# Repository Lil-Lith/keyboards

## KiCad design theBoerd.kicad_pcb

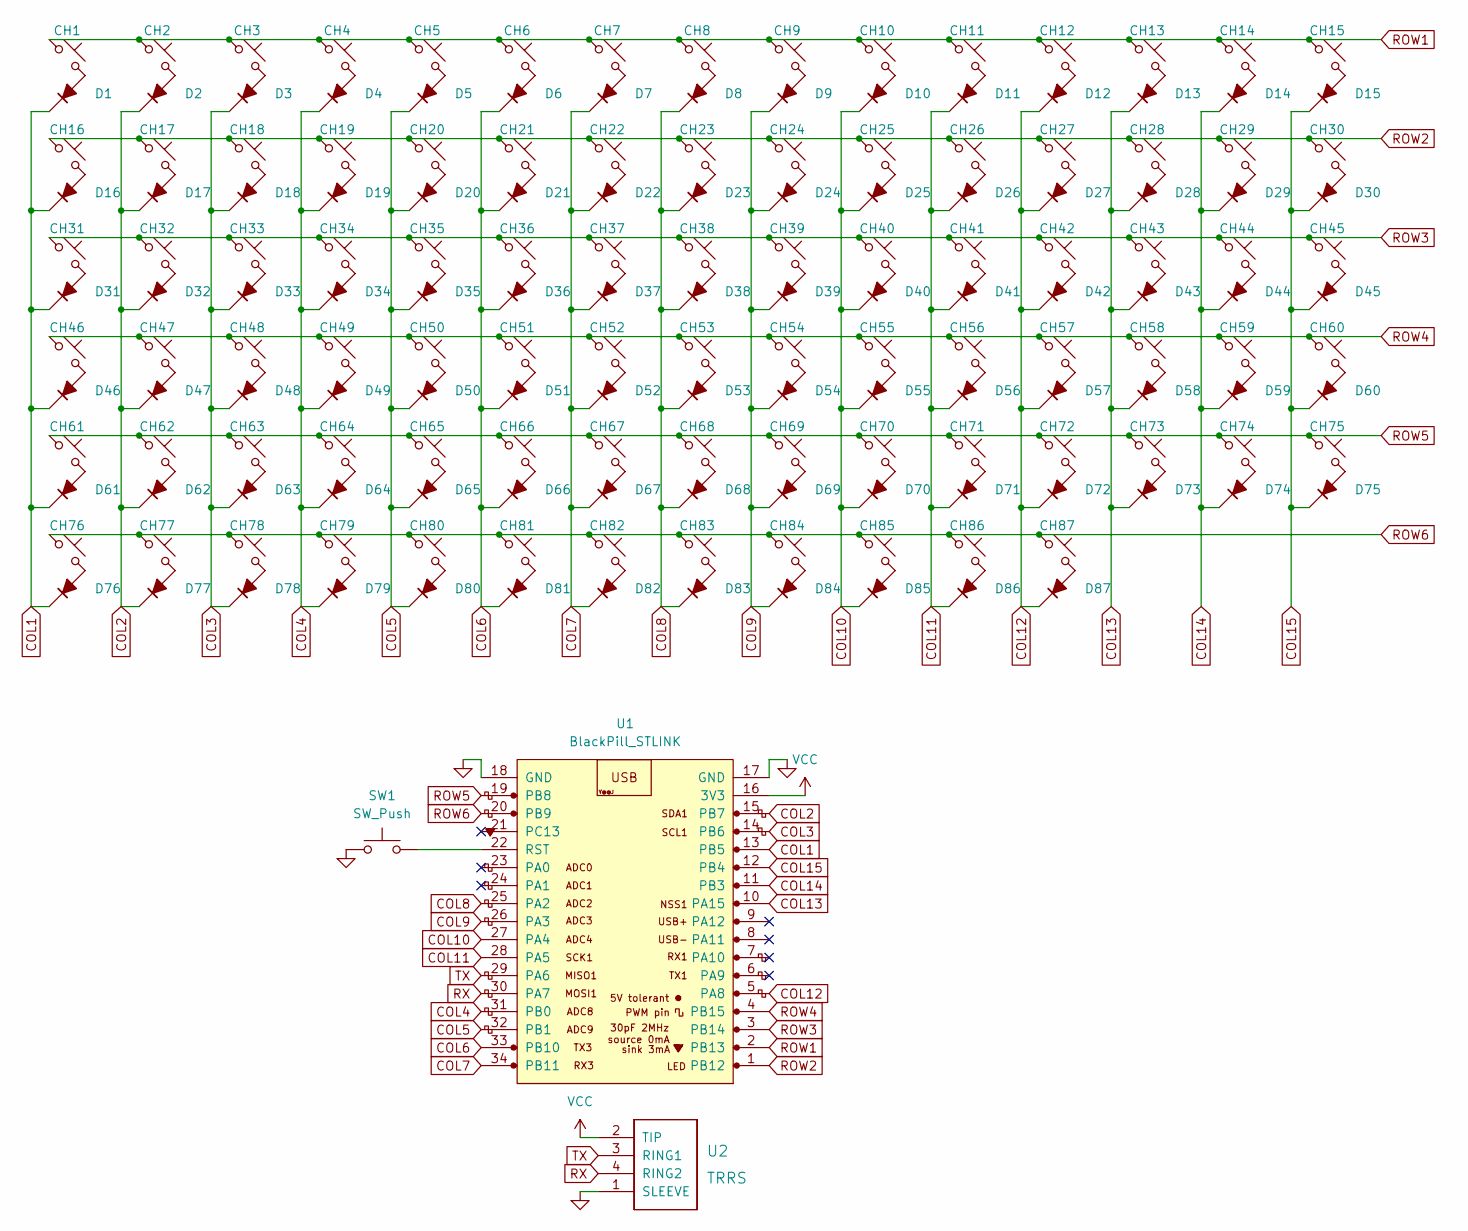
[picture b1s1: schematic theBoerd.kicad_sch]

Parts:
CH1, CH2, CH3, CH4, CH5, CH6, CH7, CH8, CH9, CH10, CH11, CH12, CH13, CH14, CH15, CH16, CH17, CH18, CH19, CH20, CH21, CH22, CH23, CH24, CH25, CH26, CH27, CH28, CH29, CH32, CH33, CH34, CH35, CH36, CH37, CH38, CH39, CH40, CH41, CH42, CH43, CH45, CH46, CH47, CH49, CH50, CH51, CH52, CH53, CH54, CH55, CH56, CH57, CH58, CH59, CH61, CH62, CH63, CH65, CH66, CH67, CH68, CH69, CH70, CH71, CH72, CH73, CH74, CH76, CH77, CH86, CH87: KS33_SW_HS; Gateron-KS33-Hotswap-1U
CH30: KS33_SW_HS; Gateron-KS33-Hotswap-2U
CH31, CH44: KS33_SW_HS; Gateron-KS33-Hotswap-1.5U
CH48: KS33_SW_HS; Gateron-KS33-Hotswap-1.75U
CH60, CH64: KS33_SW_HS; Gateron-KS33-Hotswap-2.25U
CH75: KS33_SW_HS; Gateron-KS33-Hotswap-2.75U
CH78, CH79, CH80, CH82, CH83, CH84, CH85: KS33_SW_HS; Gateron-KS33-Hotswap-1.25U
CH81: KS33_SW_HS; Gateron-KS33-Hotswap-6.25U
D1, D2, D3, D4, D5, D6, D7, D8, D9, D10, D11, D12, D13, D14, D15, D16, D17, D18, D19, D20, D21, D22, D23, D24, D25, D26, D27, D28, D29, D30, D31, D32, D33, D34, D35, D36, D37, D38, D39, D40, D41, D42, D43, D44, D45, D46, D47, D48, D49, D50, D51, D52, D53, D54, D55, D56, D57, D58, D59, D60, D61, D62, D63, D64, D65, D66, D67, D68, D69, D70, D71, D72, D73, D74, D75, D76, D77, D78, D79, D80, D81, D82, D83, D84, D85, D86, D87: D_45deg_Filled; D_1210_3225Metric
SW1: SW_Push; SW_SPDT_REED_MSDM-DT
U1: BlackPill_STLINK
U2: TRRS; TRRS-PJ-320A

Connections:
COL1: D1.1 (K), D16.1 (K), D31.1 (K), D46.1 (K), D61.1 (K), D76.1 (K), U1.13 (PB5)
COL2: D2.1 (K), D17.1 (K), D32.1 (K), D47.1 (K), D62.1 (K), D77.1 (K), U1.15 (PB7)
COL3: D3.1 (K), D18.1 (K), D33.1 (K), D48.1 (K), D63.1 (K), D78.1 (K), U1.14 (PB6)
COL4: D4.1 (K), D19.1 (K), D34.1 (K), D49.1 (K), D64.1 (K), D79.1 (K), U1.31 (PB0)
COL5: D5.1 (K), D20.1 (K), D35.1 (K), D50.1 (K), D65.1 (K), D80.1 (K), U1.32 (PB1)
COL6: D6.1 (K), D21.1 (K), D36.1 (K), D51.1 (K), D66.1 (K), D81.1 (K), U1.33 (PB10)
COL7: D7.1 (K), D22.1 (K), D37.1 (K), D52.1 (K), D67.1 (K), D82.1 (K), U1.34 (PB11)
COL8: D8.1 (K), D23.1 (K), D38.1 (K), D53.1 (K), D68.1 (K), D83.1 (K), U1.25 (PA2)
COL9: D9.1 (K), D24.1 (K), D39.1 (K), D54.1 (K), D69.1 (K), D84.1 (K), U1.26 (PA3)
COL10: D10.1 (K), D25.1 (K), D40.1 (K), D55.1 (K), D70.1 (K), D85.1 (K), U1.27 (PA4)
COL11: D11.1 (K), D26.1 (K), D41.1 (K), D56.1 (K), D71.1 (K), D86.1 (K), U1.28 (PA5)
COL12: D12.1 (K), D27.1 (K), D42.1 (K), D57.1 (K), D72.1 (K), D87.1 (K), U1.5 (PA8)
COL13: D13.1 (K), D28.1 (K), D43.1 (K), D58.1 (K), D73.1 (K), U1.10 (PA15)
COL14: D14.1 (K), D29.1 (K), D44.1 (K), D59.1 (K), D74.1 (K), U1.11 (PB3)
COL15: D15.1 (K), D30.1 (K), D45.1 (K), D60.1 (K), D75.1 (K), U1.12 (PB4)
GND: SW1.1, U1.17 (GND), U1.18 (GND), U2.1 (SLEEVE)
unnamed: CH1.2, D1.2 (A)
unnamed: CH2.2, D2.2 (A)
unnamed: CH3.2, D3.2 (A)
unnamed: CH4.2, D4.2 (A)
unnamed: CH5.2, D5.2 (A)
unnamed: CH6.2, D6.2 (A)
unnamed: CH7.2, D7.2 (A)
unnamed: CH8.2, D8.2 (A)
unnamed: CH9.2, D9.2 (A)
unnamed: CH10.2, D10.2 (A)
unnamed: CH11.2, D11.2 (A)
unnamed: CH12.2, D12.2 (A)
unnamed: CH13.2, D13.2 (A)
unnamed: CH14.2, D14.2 (A)
unnamed: CH15.2, D15.2 (A)
unnamed: CH16.2, D16.2 (A)
unnamed: CH17.2, D17.2 (A)
unnamed: CH18.2, D18.2 (A)
unnamed: CH19.2, D19.2 (A)
unnamed: CH20.2, D20.2 (A)
unnamed: CH21.2, D21.2 (A)
unnamed: CH22.2, D22.2 (A)
unnamed: CH23.2, D23.2 (A)
unnamed: CH24.2, D24.2 (A)
unnamed: CH25.2, D25.2 (A)
unnamed: CH26.2, D26.2 (A)
unnamed: CH27.2, D27.2 (A)
unnamed: CH28.2, D28.2 (A)
unnamed: CH29.2, D29.2 (A)
unnamed: CH30.2, D30.2 (A)
unnamed: CH31.2, D31.2 (A)
unnamed: CH32.2, D32.2 (A)
unnamed: CH33.2, D33.2 (A)
unnamed: CH34.2, D34.2 (A)
unnamed: CH35.2, D35.2 (A)
unnamed: CH36.2, D36.2 (A)
unnamed: CH37.2, D37.2 (A)
unnamed: CH38.2, D38.2 (A)
unnamed: CH39.2, D39.2 (A)
unnamed: CH40.2, D40.2 (A)
unnamed: CH41.2, D41.2 (A)
unnamed: CH42.2, D42.2 (A)
unnamed: CH43.2, D43.2 (A)
unnamed: CH44.2, D44.2 (A)
unnamed: CH45.2, D45.2 (A)
unnamed: CH46.2, D46.2 (A)
unnamed: CH47.2, D47.2 (A)
unnamed: CH48.2, D48.2 (A)
unnamed: CH49.2, D49.2 (A)
unnamed: CH50.2, D50.2 (A)
unnamed: CH51.2, D51.2 (A)
unnamed: CH52.2, D52.2 (A)
unnamed: CH53.2, D53.2 (A)
unnamed: CH54.2, D54.2 (A)
unnamed: CH55.2, D55.2 (A)
unnamed: CH56.2, D56.2 (A)
unnamed: CH57.2, D57.2 (A)
unnamed: CH58.2, D58.2 (A)
unnamed: CH59.2, D59.2 (A)
unnamed: CH60.2, D60.2 (A)
unnamed: CH61.2, D61.2 (A)
unnamed: CH62.2, D62.2 (A)
unnamed: CH63.2, D63.2 (A)
unnamed: CH64.2, D64.2 (A)
unnamed: CH65.2, D65.2 (A)
unnamed: CH66.2, D66.2 (A)
unnamed: CH67.2, D67.2 (A)
unnamed: CH68.2, D68.2 (A)
unnamed: CH69.2, D69.2 (A)
unnamed: CH70.2, D70.2 (A)
unnamed: CH71.2, D71.2 (A)
unnamed: CH72.2, D72.2 (A)
unnamed: CH73.2, D73.2 (A)
unnamed: CH74.2, D74.2 (A)
unnamed: CH75.2, D75.2 (A)
unnamed: CH76.2, D76.2 (A)
unnamed: CH77.2, D77.2 (A)
unnamed: CH78.2, D78.2 (A)
unnamed: CH79.2, D79.2 (A)
unnamed: CH80.2, D80.2 (A)
unnamed: CH81.2, D81.2 (A)
unnamed: CH82.2, D82.2 (A)
unnamed: CH83.2, D83.2 (A)
unnamed: CH84.2, D84.2 (A)
unnamed: CH85.2, D85.2 (A)
unnamed: CH86.2, D86.2 (A)
unnamed: CH87.2, D87.2 (A)
unnamed: SW1.2, U1.22 (RST)
ROW1: CH1.1, CH2.1, CH3.1, CH4.1, CH5.1, CH6.1, CH7.1, CH8.1, CH9.1, CH10.1, CH11.1, CH12.1, CH13.1, CH14.1, CH15.1, U1.2 (PB13)
ROW2: CH16.1, CH17.1, CH18.1, CH19.1, CH20.1, CH21.1, CH22.1, CH23.1, CH24.1, CH25.1, CH26.1, CH27.1, CH28.1, CH29.1, CH30.1, U1.1 (PB12)
ROW3: CH31.1, CH32.1, CH33.1, CH34.1, CH35.1, CH36.1, CH37.1, CH38.1, CH39.1, CH40.1, CH41.1, CH42.1, CH43.1, CH44.1, CH45.1, U1.3 (PB14)
ROW4: CH46.1, CH47.1, CH48.1, CH49.1, CH50.1, CH51.1, CH52.1, CH53.1, CH54.1, CH55.1, CH56.1, CH57.1, CH58.1, CH59.1, CH60.1, U1.4 (PB15)
ROW5: CH61.1, CH62.1, CH63.1, CH64.1, CH65.1, CH66.1, CH67.1, CH68.1, CH69.1, CH70.1, CH71.1, CH72.1, CH73.1, CH74.1, CH75.1, U1.19 (PB8)
ROW6: CH76.1, CH77.1, CH78.1, CH79.1, CH80.1, CH81.1, CH82.1, CH83.1, CH84.1, CH85.1, CH86.1, CH87.1, U1.20 (PB9)
RX: U1.30 (PA7), U2.4 (RING2)
TX: U1.29 (PA6), U2.3 (RING1)
VCC: U1.16 (3V3), U2.2 (TIP)

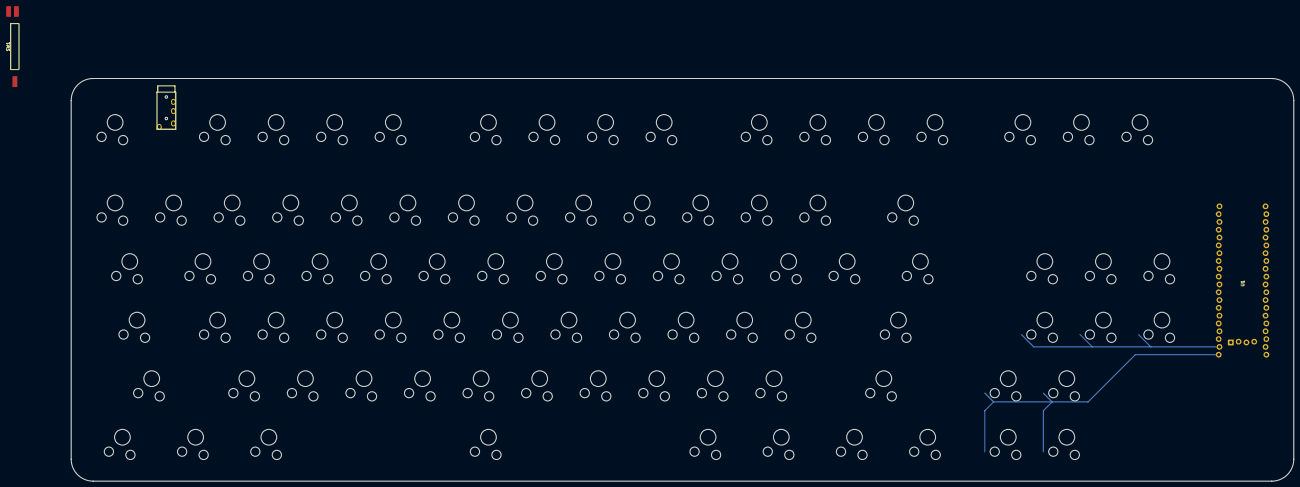
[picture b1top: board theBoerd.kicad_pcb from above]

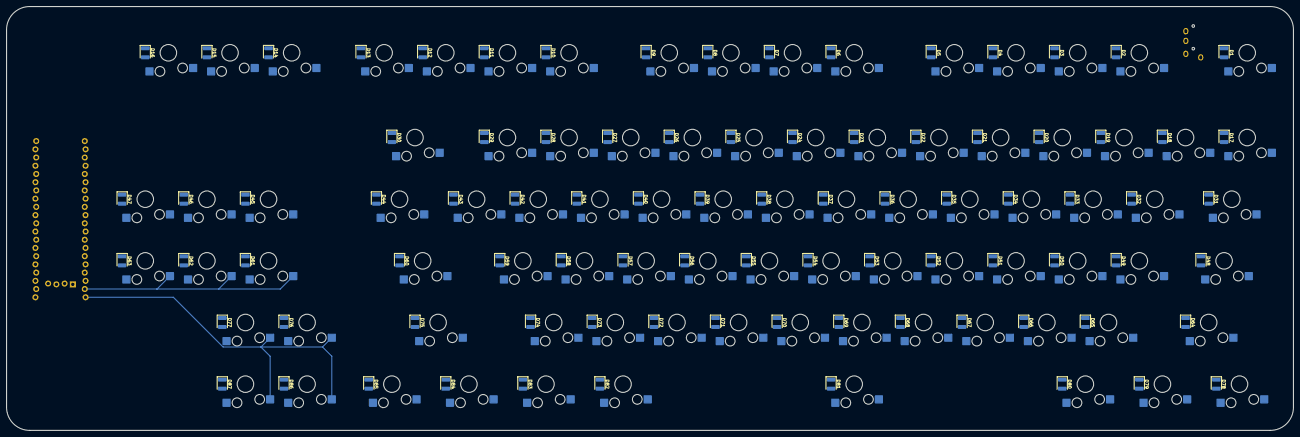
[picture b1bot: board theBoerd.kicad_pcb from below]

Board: 2 copper layers, 397.7 x 131.0 mm, 177 parts (174 on the bottom side), 113 nets.

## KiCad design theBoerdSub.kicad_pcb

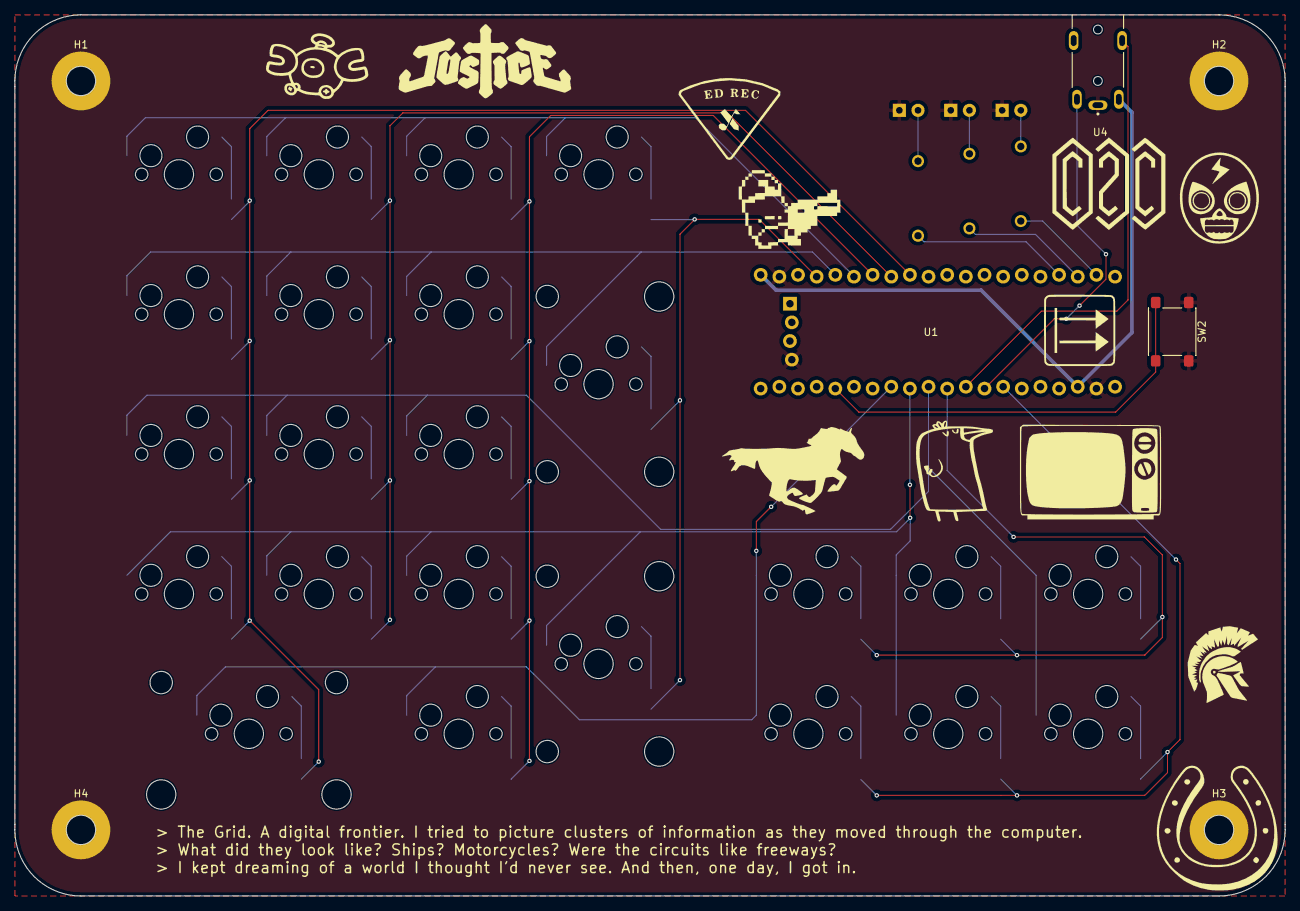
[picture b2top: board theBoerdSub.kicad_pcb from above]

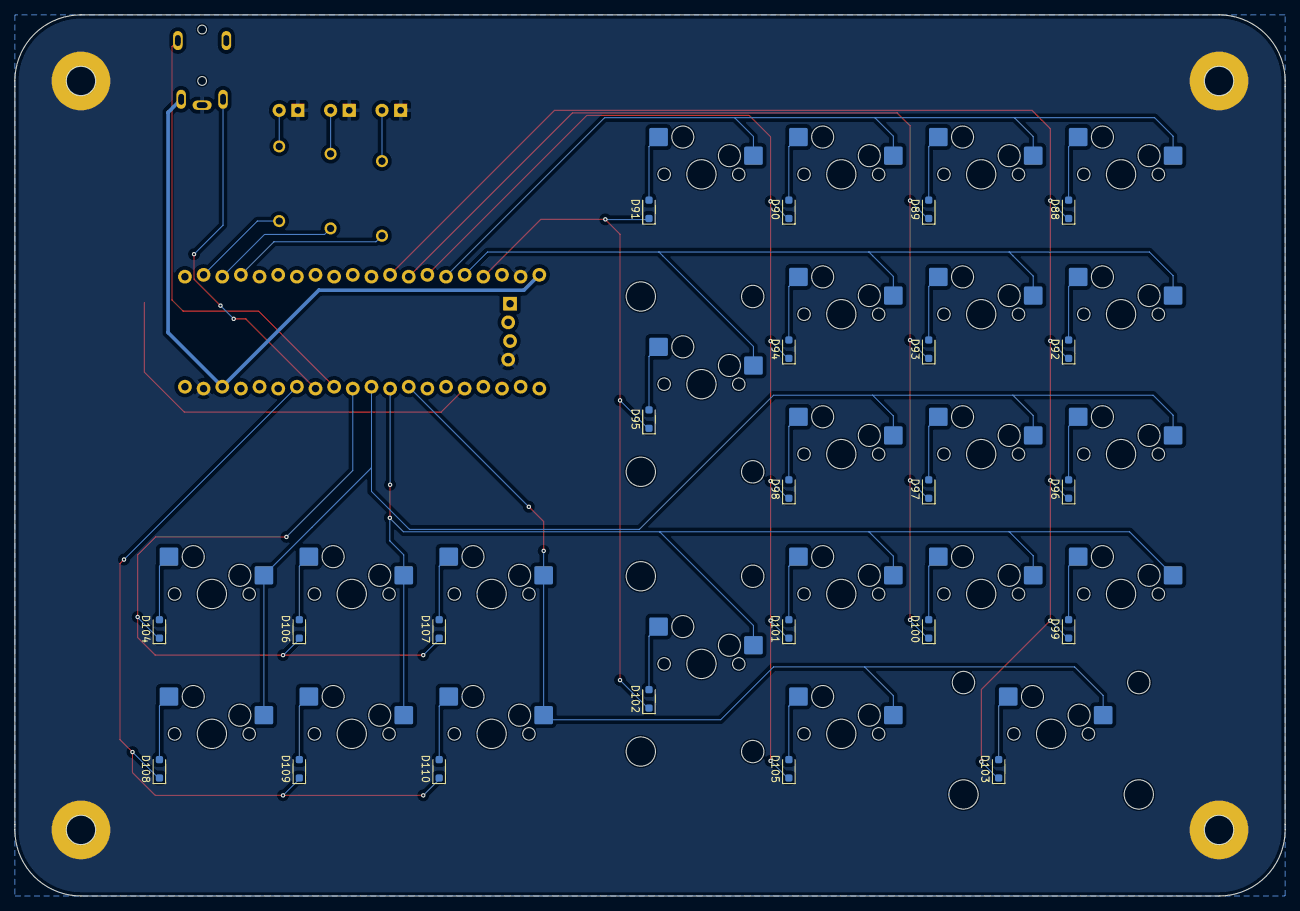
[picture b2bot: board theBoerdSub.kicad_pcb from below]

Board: 2 copper layers, 173.0 x 120.0 mm, 59 parts (46 on the bottom side), 45 nets.

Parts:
CH88, CH89, CH90, CH91, CH92, CH93, CH94, CH96, CH97, CH98, CH99, CH100, CH101, CH104, CH105, CH106, CH107, CH108, CH109, CH110: KS33_SW_HS; MX-Hotswap-1U
CH95, CH102: KS33_SW_HS; MX-Hotswap-2U-Vertical
CH103: KS33_SW_HS; MX-Hotswap-2U
D88, D89, D90, D91, D92, D93, D94, D95, D96, D97, D98, D99, D100, D101, D102, D103, D104, D105, D106, D107, D108, D109, D110: D_45deg_Filled; D_SOD-323_HandSoldering
D111, D112, D113: LED; LED_D5.0mm_evil
H1, H2, H3, H4: MountingHole_Pad; MountingHole_4mm_Pad
R1, R2, R3: R; Resistor
SW2: SW_Push; SW_SPST_PTS645Sx43SMTR92
U1: BlackPill_STLINK
U4: TRRS; TENSILITY_54-00174

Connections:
NCOL1: D88.1 (K), D92.1 (K), D96.1 (K), D99.1 (K), D103.1 (K), U1.12 (PB4)
NCOL2: D89.1 (K), D93.1 (K), D97.1 (K), D100.1 (K), U1.13 (PB5)
NCOL3: D90.1 (K), D94.1 (K), D98.1 (K), D101.1 (K), D105.1 (K), U1.14 (PB6)
NCOL4: D91.1 (K), D95.1 (K), D102.1 (K), U1.17 (PB9)
NCOL5: D104.1 (K), D106.1 (K), D107.1 (K), U1.31 (PA5)
NCOL6: D108.1 (K), D109.1 (K), D110.1 (K), U1.34 (PB0)
NGND: D111.1 (K), D112.1 (K), D113.1 (K), H1.1, H2.1, H3.1, H4.1, SW2.1, U1.19 (GND), U1.39 (GND), U1.44 (GND), U4.1
NROW1: CH88.1, CH89.1, CH90.1, CH91.1, U1.15 (PB7)
NROW2: CH92.1, CH93.1, CH94.1, CH95.1, U1.16 (PB8)
NROW3: CH96.1, CH97.1, CH98.1, CH104.1, CH108.1, U1.30 (PA4)
NROW4: CH99.1, CH100.1, CH101.1, CH102.1, CH106.1, CH109.1, U1.29 (PA3)
NROW5: CH103.1, CH105.1, CH107.1, CH110.1, U1.28 (PA2)
NRX: U1.32 (PA6), U4.4_1
NTX: U1.33 (PA7), U4.3
NVCC: U1.20 (3V3), U1.38 (3V3), U4.2
unnamed: CH88.2, D88.2 (A)
unnamed: CH89.2, D89.2 (A)
unnamed: CH90.2, D90.2 (A)
unnamed: CH91.2, D91.2 (A)
unnamed: CH92.2, D92.2 (A)
unnamed: CH93.2, D93.2 (A)
unnamed: CH94.2, D94.2 (A)
unnamed: CH95.2, D95.2 (A)
unnamed: CH96.2, D96.2 (A)
unnamed: CH97.2, D97.2 (A)
unnamed: CH98.2, D98.2 (A)
unnamed: CH99.2, D99.2 (A)
unnamed: CH100.2, D100.2 (A)
unnamed: CH101.2, D101.2 (A)
unnamed: CH102.2, D102.2 (A)
unnamed: CH103.2, D103.2 (A)
unnamed: CH104.2, D104.2 (A)
unnamed: CH105.2, D105.2 (A)
unnamed: CH106.2, D106.2 (A)
unnamed: CH107.2, D107.2 (A)
unnamed: CH108.2, D108.2 (A)
unnamed: CH109.2, D109.2 (A)
unnamed: CH110.2, D110.2 (A)
unnamed: D111.2 (A), R1.2
unnamed: D112.2 (A), R2.2
unnamed: D113.2 (A), R3.2
unnamed: R1.1, U1.2 (PB13)
unnamed: R2.1, U1.3 (PB14)
unnamed: R3.1, U1.4 (PB15)
unnamed: SW2.2, U1.25 (~RESET)

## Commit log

2026-02-09 Setup
2026-02-19 Keebio Parts lib added, Schematic changes
2026-03-03 Project Restart
2026-03-17 rebuild like #3 i think
2026-04-01 Nearly Finalized Boards
2026-04-02 Manufacturing Prep
2026-04-02 Gerber Rezip
2026-04-03 JLCPCB Fix
    - Added edge cuts to center of mounting holes
2026-04-07 Silkscreen additions
2026-04-08 Diode and Jack fixes, Silkscreen additons
    Diode and TRRS Jack footprints replaced with available parts.
2026-04-09 Final Silkscreen Additions (?)
2026-04-09 Keebio causes me rage
2026-04-13 .STEP Files Creation
2026-04-15 Key Labeling
2026-05-01 PDF Exports
